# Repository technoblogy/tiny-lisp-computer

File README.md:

# Tiny Lisp Computer
A self-contained computer with its own display and keyboard, based on an ATmega328 or ATmega1284, that you can program in Lisp.
For more information see:

Tiny Lisp Computer (ATmega328): http://www.technoblogy.com/show?1GX1

Tiny Lisp Computer 2 (ATmega1284): http://www.technoblogy.com/show?1INT

Tiny Lisp Computer 2 PCB version: http://www.technoblogy.com/show?1KTO

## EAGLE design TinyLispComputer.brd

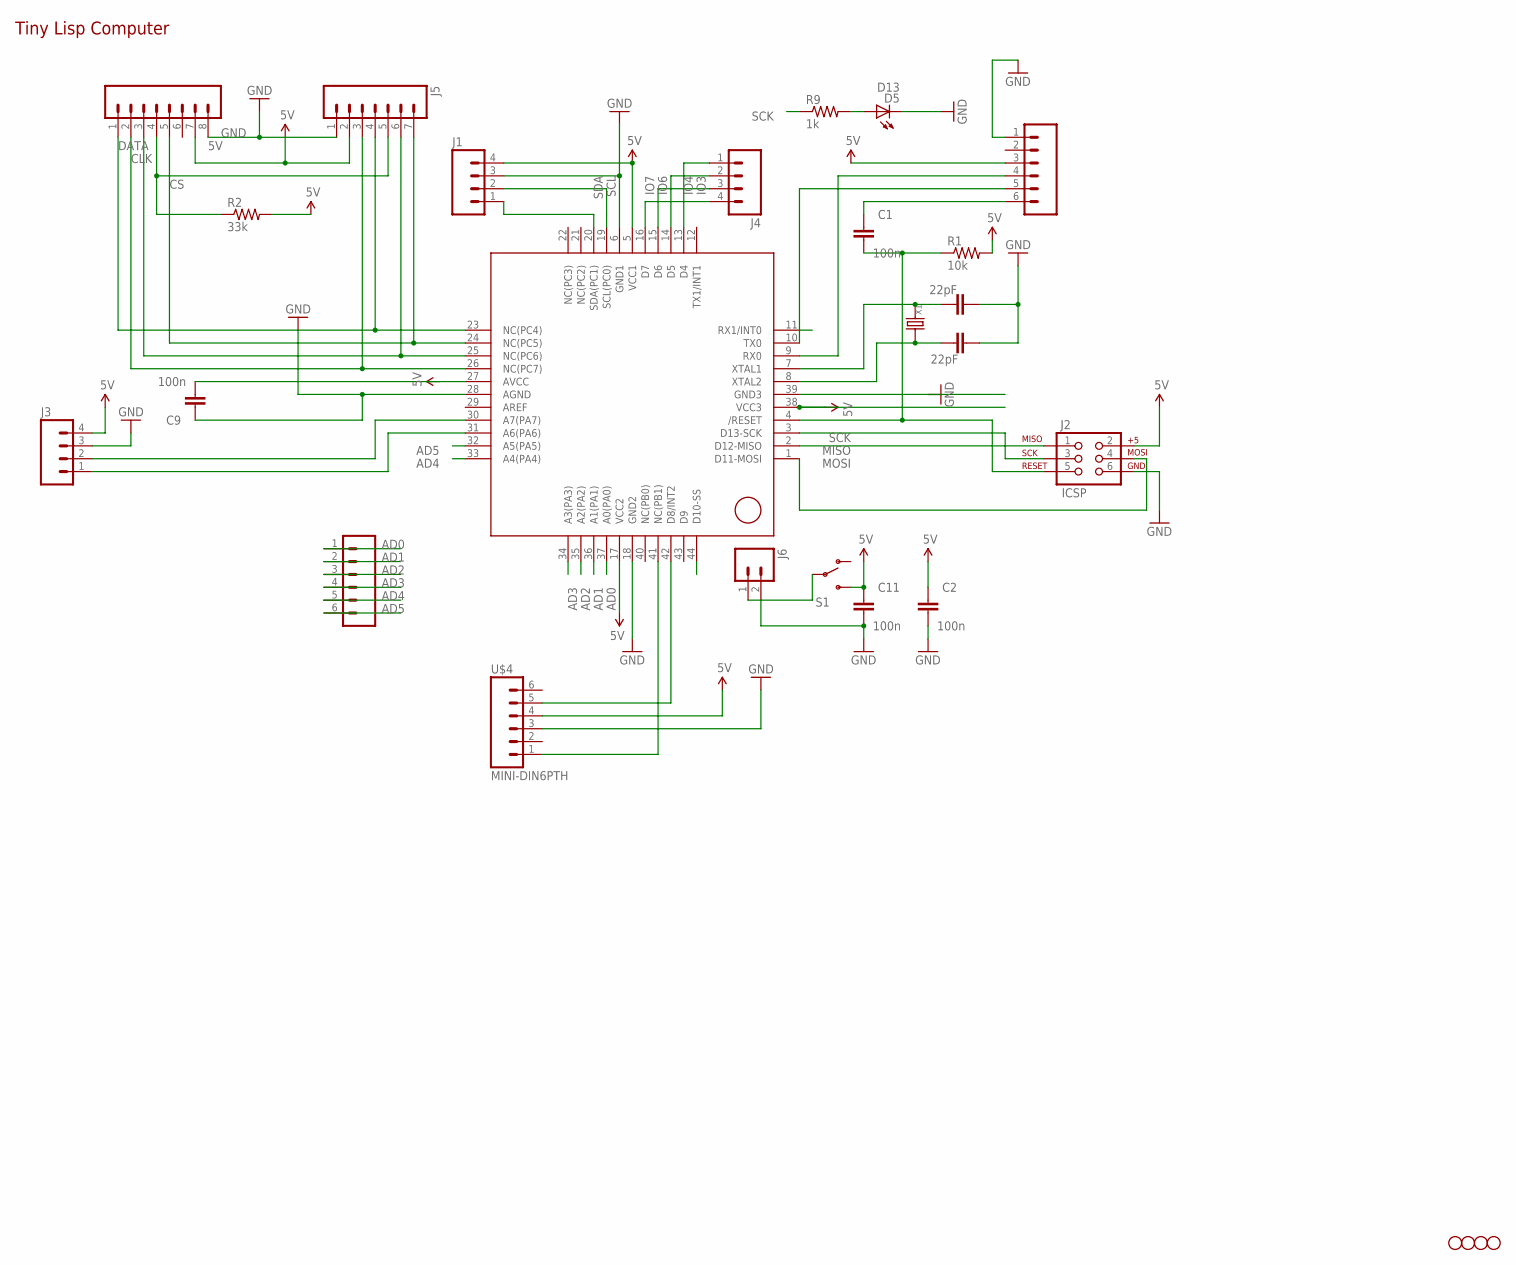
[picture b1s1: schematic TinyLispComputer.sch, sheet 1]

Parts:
C1, C2, C9, C11: 100n; 0603-CAP
C12, C13: 22pF; 0603-CAP
D5: D13; CHIPLED_0805
J1, J3, J4: M04LONGPADS; 1X04_LONGPADS
J2: ICSP; 2X3
J5: M07; 1X07
J6: M021X02_NO_SILK; 1X02_NO_SILK
JP1, JP11: M06LONGPADS; 1X06_LONGPADS
JP3, JP4, JP5, JP6: STAND-OFF
OLED: M08; 1X08_ROUND
R1: 10k; 0805
R2: 33k; 0805
R9: 1k; 0805
S1: SWITCH-SPDTPTH; SWITCH-SPDT
U3: ATMEGA1284P; TQFP44
U$4: MINI-DIN6PTH; MINI-DIN6
X1: CRYSTAL-0500290P1; 2P-SMD-5.0X3.2

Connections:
5V: C2.1, C9.2, C11.1, J1.4, J2.2, J3.4, J5.2, JP1.3, OLED.7, R1.2, R2.2, S1.3 (S), U3.5 (VCC1), U3.17 (VCC2), U3.27 (AVCC), U3.38 (VCC3), U$4.4
AD0: JP11.1, U3.37 (A0(PA0))
AD1: JP11.2, U3.36 (A1(PA1))
AD2: JP11.3, U3.35 (A2(PA2))
AD3: JP11.4, U3.34 (A3(PA3))
AD4: JP11.5, U3.33 (A4(PA4))
AD5: JP11.6, U3.32 (A5(PA5))
CLK: J5.6, OLED.3, U3.25 (NC(PC6))
CS: J5.4, OLED.1, U3.23 (NC(PC4))
DATA: J5.3, OLED.2, U3.26 (NC(PC7))
GND: C2.2, C9.1, C11.2, C12.1, C13.1, D5.C, J1.3, J2.6, J3.3, J5.1, J6.2, JP1.1, OLED.8, U3.6 (GND1), U3.18 (GND2), U3.28 (AGND), U3.39 (GND3), U$4.3
IO2: U3.11 (RX1/INT0)
IO3: J4.1, U3.13 (D4)
IO4: J4.2, U3.14 (D5)
IO6: J4.3, U3.15 (D6)
IO7: J4.4, U3.16 (D7)
MISO: J2.1, U3.2 (D12-MISO)
MOSI: J2.4, U3.1 (D11-MOSI)
unnamed: J5.7, OLED.5, U3.24 (NC(PC5))
unnamed: J6.1, S1.2
unnamed: C1.1, JP1.6
unnamed: J5.5, OLED.4, R2.1
unnamed: J3.1, U3.31 (A6(PA6))
unnamed: C1.2, J2.5, R1.1, U3.4 (/RESET)
unnamed: U3.42 (D8/INT2), U$4.5
unnamed: U3.41 (NC(PB1)), U$4.1
unnamed: J3.2, U3.30 (A7(PA7))
unnamed: D5.A, R9.2
unnamed: C13.2, U3.8 (XTAL2), X1.2
unnamed: C12.2, U3.7 (XTAL1), X1.1
RX-I: JP1.4, U3.9 (RX0)
SCK: J2.3, R9.1, U3.3 (D13-SCK)
SCL: J1.2, U3.19 (SCL(PC0))
SDA: J1.1, U3.20 (SDA(PC1))
SS: U3.44 (D10-SS)
TX-O: JP1.5, U3.10 (TX0)

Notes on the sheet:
Tiny Lisp Computer

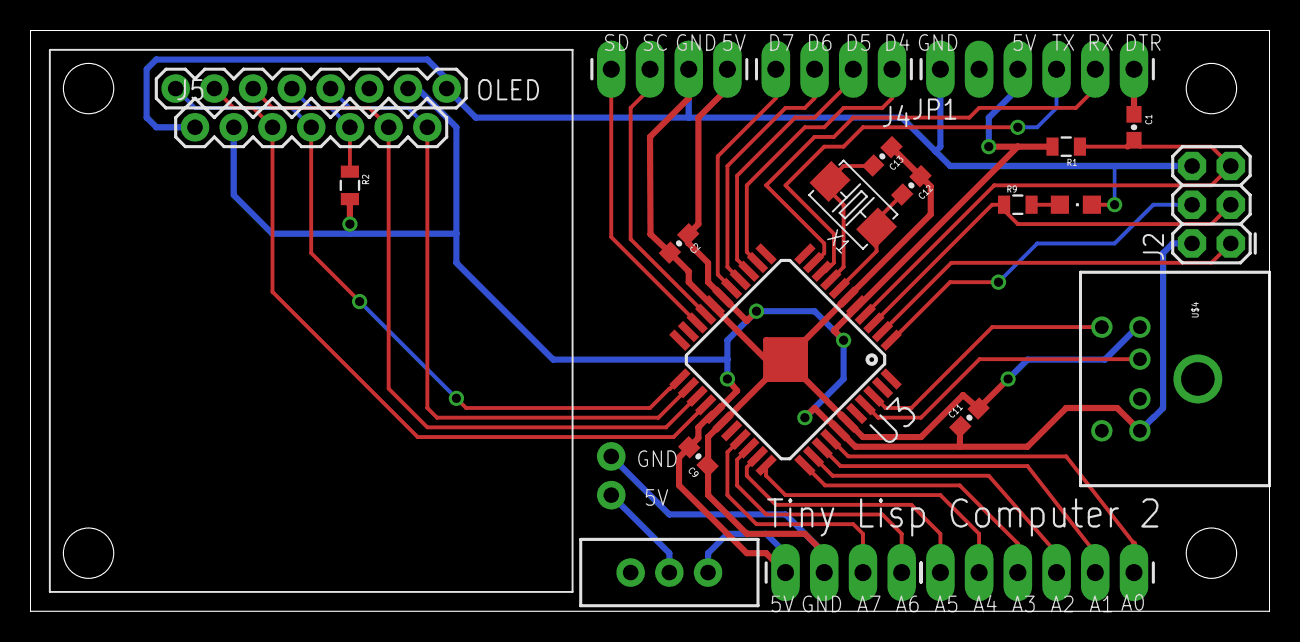
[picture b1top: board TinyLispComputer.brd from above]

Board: 2 copper layers, 81.3 x 38.1 mm, 27 parts (0 on the bottom side), 34 nets.

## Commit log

2016-10-18 Tiny Lisp Computer 2 - 18th October 2016
    Includes: ATmega1284 support, parenthesis matching, optional program entry via the Arduino IDE serial monitor, and a built-in program editor.
2016-10-18 Added Tiny Lisp Computer 2
2016-10-19 License
2017-02-06 Tiny Lisp Computer 2 - uLisp 1.5 - 24th January 2017
2017-02-06 Eagle files - Version 1

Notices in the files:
parts and their libraries:
SparkFun-Capacitors: Licensing: CC v3.0 Share-Alike You are welcome to use this library for commercial purposes.
SparkFun-Electromechanical: Licensing: Creative Commons ShareAlike 4.0 International - https://creativecommons.org/licenses/by-sa/4.0
